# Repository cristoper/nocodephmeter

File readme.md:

This is a pH meter with temperature compensation and digital readout (but no microcontroller) created as part of [Hackaday's 2023 Op-Amp Challenge](https://hackaday.io/contest/190312-op-amp-challenge). It is still under active development. For more information see it's project page:

https://hackaday.io/project/191424-no-code-ph-meter

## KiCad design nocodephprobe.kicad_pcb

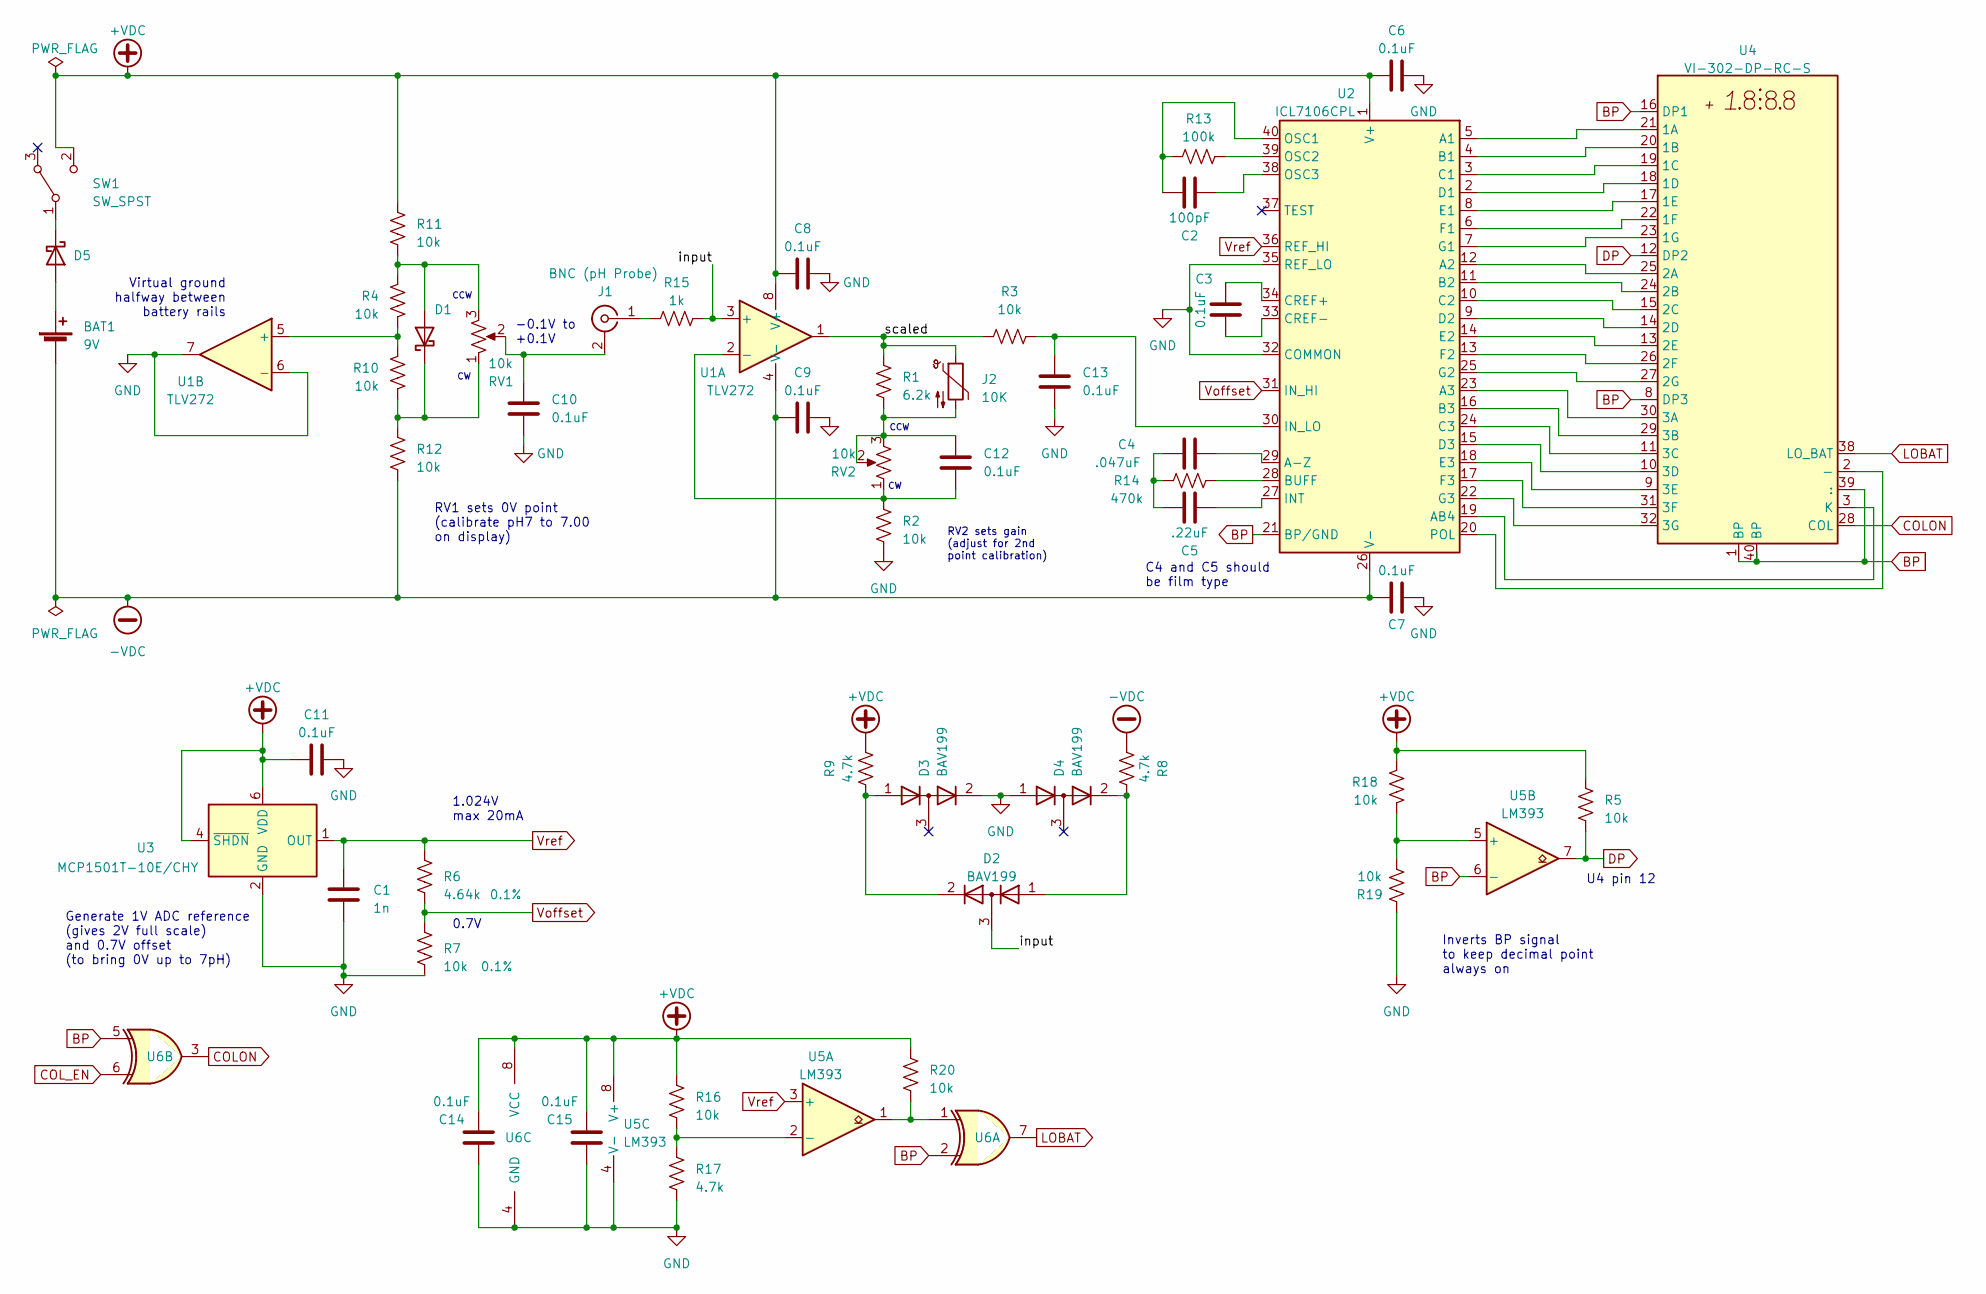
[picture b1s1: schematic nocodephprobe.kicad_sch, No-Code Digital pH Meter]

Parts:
BAT1: 9V; JST_XH_B2B-XH-A_1x02_P2.50mm_Vertical
C1: 1n; C_0805_2012Metric_Pad1.18x1.45mm_HandSolder
C2: 100pF; C_0805_2012Metric_Pad1.18x1.45mm_HandSolder
C3, C6, C7, C8, C9, C10, C11, C12, C13, C14, C15: 0.1uF; C_0805_2012Metric_Pad1.18x1.45mm_HandSolder
C4: .047uF; C_0805_2012Metric_Pad1.18x1.45mm_HandSolder
C5: .22uF; C_Rect_L18.0mm_W6.0mm_P15.00mm_FKS3_FKP3
D1, D5: BAT54-Q; TSOT-23_HandSoldering
D2, D3, D4: BAV199; SOT-23
J1: BNC (pH Probe); BNC_Amphenol_031-6575_Horizontal; digikey 2057-RF1-01K-D-00-50-BK-HDW-ND
J2: 10K; KYCON_STX-3120-3B
R1: 6.2k; R_0805_2012Metric_Pad1.20x1.40mm_HandSolder
R2, R3, R4, R5, R10, R11, R12, R16, R18, R19, R20: 10k; R_0805_2012Metric_Pad1.20x1.40mm_HandSolder
R6: 4.64k; R_0805_2012Metric_Pad1.20x1.40mm_HandSolder; Tolerance 0.1%
R7: 10k; R_0805_2012Metric_Pad1.20x1.40mm_HandSolder; Tolerance 0.1%
R8, R9, R17: 4.7k; R_0805_2012Metric_Pad1.20x1.40mm_HandSolder
R13: 100k; R_0805_2012Metric_Pad1.20x1.40mm_HandSolder
R14: 470k; R_0805_2012Metric_Pad1.20x1.40mm_HandSolder
R15: 1k; R_0805_2012Metric_Pad1.20x1.40mm_HandSolder
RV1, RV2: 10k; JST_XH_B3B-XH-A_1x03_P2.50mm_Vertical
SW1: SW_SPST; JST_XH_B2B-XH-A_1x02_P2.50mm_Vertical
U1: TLV272; SOIC-8_3.9x4.9mm_P1.27mm
U2: ICL7106CPL; DIP-40_W15.24mm
U3: MCP1501T-10E/CHY; SOT-23-6
U4: VI-302-DP-RC-S; DE113-XX-XX
U5: LM393; TSSOP-8_4.4x3mm_P0.65mm
U6: 74HC2G86; TSSOP-8_3x3mm_P0.65mm

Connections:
+VDC: C6.1, C8.1, C11.1, C14.1, C15.1, R5.2, R9.1, R11.2, R16.2, R18.1, R20.2, SW1.2 (C), U1.8 (V+), U2.1 (V+), U3.4 (~SHDN), U3.6 (VDD), U5.8 (V+), U6.8 (VCC)
-VDC: BAT1.2 (-), C7.1, C9.1, R8.2, R12.1, U1.4 (V-), U2.26 (V-)
/input: D2.3 (common), R15.1, U1.3 (+)
/scaled: J2.1, R1.2, R3.1, U1.1
BP: U2.21 (BP/GND), U4.1 (BP), U4.8 (DP3), U4.16 (DP1), U4.39 (:), U4.40 (BP), U5.6 (-), U6.2, U6.5
COLON: U4.28 (COL), U6.3
COL_EN: U6.6
DP: R5.1, U4.12 (DP2), U5.7
GND: C1.2, C6.2, C7.2, C8.2, C9.2, C10.1, C11.2, C13.1, C14.2, C15.2, D3.2 (K), D4.1 (A), R2.1, R7.1, R17.1, R19.2, U1.6 (-), U1.7, U2.32 (COMMON), U2.35 (REF_LO), U3.2 (GND), U3.3 (GND), U3.5 (GND), U5.4 (V-), U6.4 (GND)
LOBAT: U4.38 (LO_BAT), U6.7
unnamed: BAT1.1 (+), D5.1 (A)
unnamed: C4.2, C5.2, R14.2
unnamed: C12.2, J2.5, R1.1, RV2.2, RV2.3
unnamed: D1.1 (A), R4.2, R11.1, RV1.3
unnamed: D1.3 (K), R10.1, R12.2, RV1.1
unnamed: D2.1 (A), D4.2 (K), R8.1
unnamed: D2.2 (K), D3.1 (A), R9.2
unnamed: D5.3 (K), SW1.1 (B)
unnamed: C10.2, J1.2 (Ext), RV1.2
unnamed: J1.1 (In), R15.2
unnamed: R20.1, U5.1, U6.1
unnamed: C12.1, R2.2, RV2.1, U1.2 (-)
unnamed: R4.1, R10.2, U1.5 (+)
unnamed: U2.5 (A1), U4.21 (1A)
unnamed: U2.12 (A2), U4.25 (2A)
unnamed: U2.23 (A3), U4.30 (3A)
unnamed: C4.1, U2.29 (A-Z)
unnamed: U2.19 (AB4), U4.3 (K)
unnamed: U2.4 (B1), U4.20 (1B)
unnamed: U2.11 (B2), U4.24 (2B)
unnamed: U2.16 (B3), U4.29 (3B)
unnamed: R14.1, U2.28 (BUFF)
unnamed: U2.3 (C1), U4.19 (1C)
unnamed: U2.10 (C2), U4.15 (2C)
unnamed: U2.24 (C3), U4.11 (3C)
unnamed: C3.1, U2.34 (CREF+)
unnamed: C3.2, U2.33 (CREF-)
unnamed: U2.2 (D1), U4.18 (1D)
unnamed: U2.9 (D2), U4.14 (2D)
unnamed: U2.15 (D3), U4.10 (3D)
unnamed: U2.8 (E1), U4.17 (1E)
unnamed: U2.14 (E2), U4.13 (2E)
unnamed: U2.18 (E3), U4.9 (3E)
unnamed: U2.6 (F1), U4.22 (1F)
unnamed: U2.13 (F2), U4.26 (2F)
unnamed: U2.17 (F3), U4.31 (3F)
unnamed: U2.7 (G1), U4.23 (1G)
unnamed: U2.25 (G2), U4.27 (2G)
unnamed: U2.22 (G3), U4.32 (3G)
unnamed: C5.1, U2.27 (INT)
unnamed: C13.2, R3.2, U2.30 (IN_LO)
unnamed: C2.2, R13.1, U2.40 (OSC1)
unnamed: R13.2, U2.39 (OSC2)
unnamed: C2.1, U2.38 (OSC3)
unnamed: U2.20 (POL), U4.2 (-)
unnamed: R16.1, R17.2, U5.2 (-)
unnamed: R18.2, R19.1, U5.5 (+)
Voffset: R6.1, R7.2, U2.31 (IN_HI)
Vref: C1.1, R6.2, U2.36 (REF_HI), U3.1 (OUT), U5.3 (+)

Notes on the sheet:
U4 pin 12
C4 and C5 should be film type
1.024V max 20mA
RV2 sets gain (adjust for 2nd point calibration)
Virtual ground halfway between battery rails
RV1 sets 0V point (calibrate pH7 to 7.00 on display)
Generate 1V ADC reference (gives 2V full scale) and 0.7V offset (to bring 0V up to 7pH)
-0.1V to +0.1V
0.7V
CCW
Inverts BP signal to keep decimal point always on

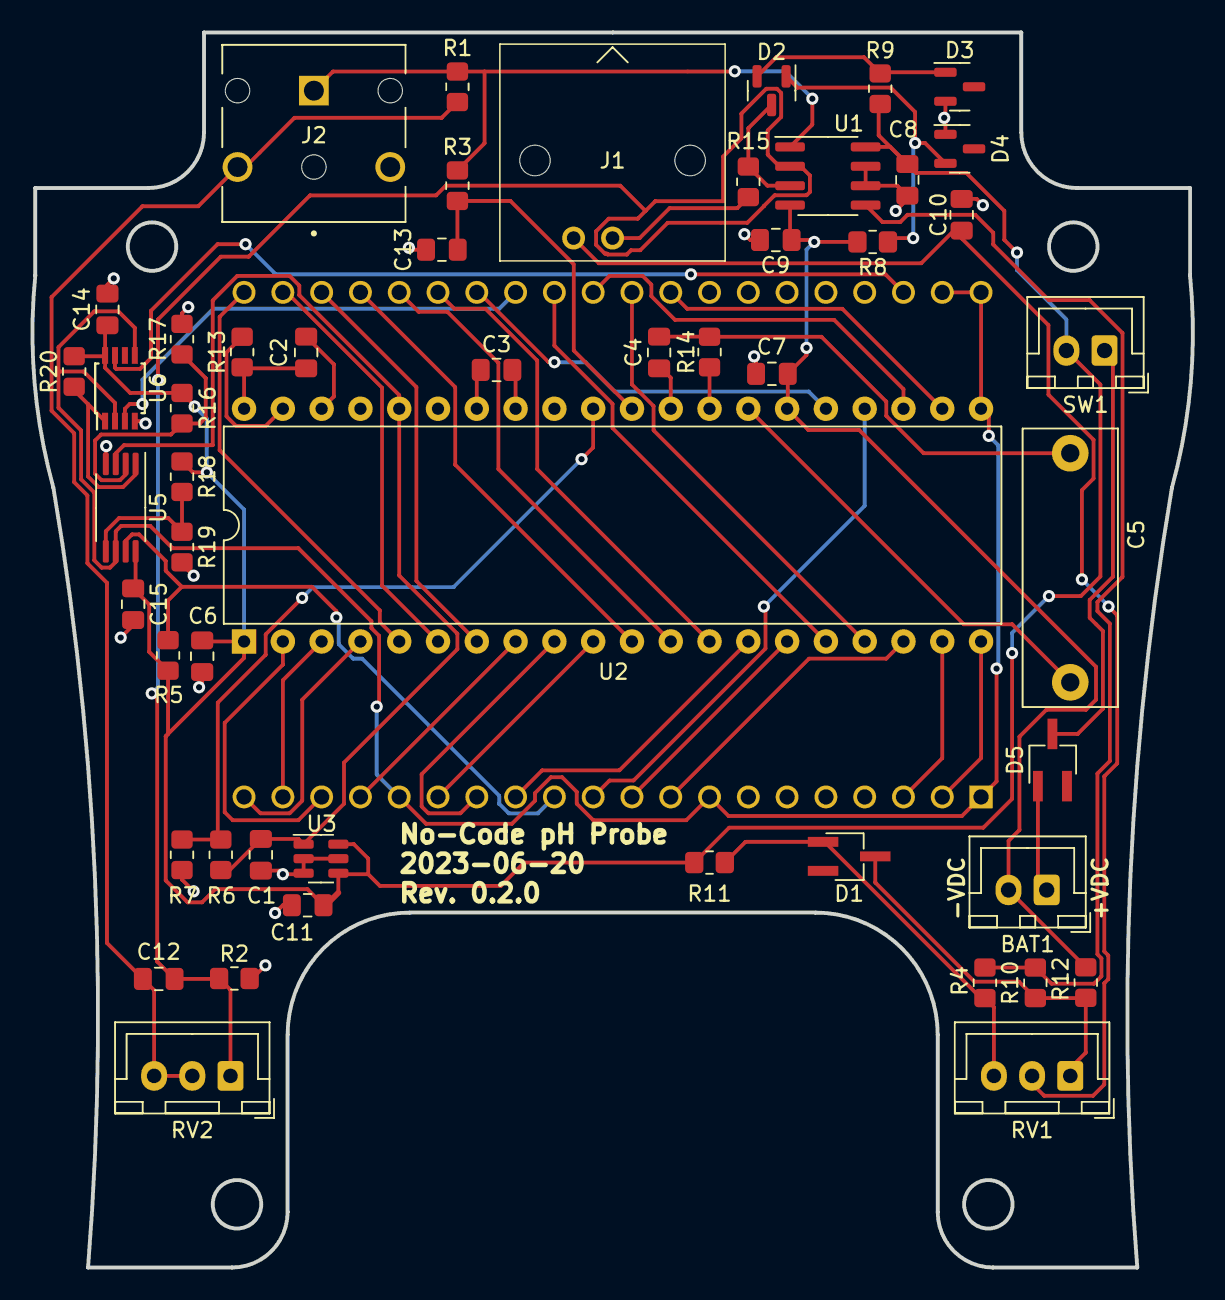
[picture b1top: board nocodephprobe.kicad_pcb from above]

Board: 2 copper layers, 76.0 x 80.9 mm, 52 parts (1 on the bottom side), 58 nets.

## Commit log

2023-05-20 Initial commit: finished basic schematic capture
    Now to choose enclosure and lay out PCB.
2023-05-23 Use 10k pots instead of 100k
2023-05-23 Track board edge drawings
2023-05-23 Use only 1 diode in offset circuit
2023-05-24 Add header footprints to bat and pots
2023-05-24 Add some 3d models
    Including a model for the bnc connector drawn in FreeCAD.
2023-05-24 Fix PCB bosses on board outline!
2023-05-24 Track bnc model
2023-05-25 Add cutout for pots to pcb outline
2023-05-25 track c5 3d model
2023-05-25 Initial routing of nets
    No DRC errors, but some mess vias and traces.
2023-05-26 Remove redundant voltage divider
    This removes two resistors.
2023-05-26 Add revision and github text to silkscreen
2023-05-26 Rework a few traces
2023-05-26 Add guard ring around probe input
2023-05-26 Correct Cref (C3 value)
2023-05-27 Update some gerber settings for jlcpcb
2023-05-27 Add silkscreen labels to power nets
2023-05-28 pcb: move trace away from edge
2023-05-28 pcb: make d1 and r12 more compact
2023-05-28 pcb: move components away from edge and eliminate 2 vias
2023-05-28 pcb: eliminate 2 vias
2023-05-30 schematic: add decoupling caps to op-amp
2023-05-30 Fix op-amp power supply
    Add an 7805 linear regulator to keep voltage within max supply, and add
    decoupling caps.
2023-06-02 Remove fmask all the way around guard trace
    Based on prototype pcbs from jlcpcb, I don't think solder bridges will
    be an issue.
2023-06-03 pcb: fix lcd footprint
    The pins are actually 1.27mm offset (so a 2.54mm wider footprint):
    https://media.digikey.com/pdf/Data%20Sheets/Varitronix%20PDFs/Displays.pdf
2023-06-04 Transpose R6 and R7
    In the prototype the voffset was 0.3V instead of 0.7V!
2023-06-04 pcb: fix LCD pinout!
    Plus it was much easier to route with the correct pin numbering (many
    fewer vias)
2023-06-05 schematic: add pn and datasheet to ntc
2023-06-05 Add decoupling caps to potentiometers
    This also changes the 7805 to a smaller footprint
2023-06-05 Change D1 to a Schottky diode
    This will reduce the range of the zero calibration from +/- 0.3V to +/-
    0.15V and make the setting less finicky.
2023-06-05 Flip pots so that CW increases pH during calibration
2023-06-05 Track label template
2023-06-05 pcb: update silkscreen for new github url
2023-06-05 Add MIT license.txt
2023-06-06 Add header for power switch
2023-06-06 Add basic readme
2023-06-06 Regulate entire circuit to 5V
    Though in the future I'd like to run the 7106 directly from the battery,
    that requires centering the 7805 and lmv358a at the virtual ground.
2023-06-06 Ignore hackaday/ dir
2023-06-06 pcb: update PCB to reflect schematic (power 7106 from 5V)
    I am really unhappy with the power routing and need to rework the whole
    power system so the 7106 can be powered directly from the battery
    anyway.
2023-06-06 schematic: tidy power switch
2023-06-09 schematic: simplify power and decoupling
    The big change is switch from the lmv358a to the tlv272:
    - TLV272 can operate from up to 16.5V supply, which means we can run it
    directly from the 9V battery (no 7805 or zeners required)
    - It has better typical Vos (500uV), Input Offset Current (1pA), and
    Input Bias Current (1PA)
    - It has worse max offset specs (Vos=5mV, Iio/Iib = 60pA), but they
2023-06-09 pcb: make cutouts for pots larger
    This makes it less critical to drill holes in panel at exact location
2023-06-11 pcb: route improved power and headers
2023-06-11 pcb: move switch header to above C5
2023-06-11 pcb: use 2-pin header for RV2
2023-06-14 Implement [optional] input protection
    D2 will clamp the input to 3 diode drops from either rail (~1.8V). This
    keeps the input within the safe range for the TLV272. R15 limits the
    current in case of overvoltage. The diodes in D3 and D4 set a bias point
    two diode drops below the positive rail and above the negative rail to
    minimize the reverse voltage (and therefore leakage current) across the
    D2 diodes.
2023-06-14 Specify cheaper Schottky diodes
    Also add one as reverse-voltage protection to protect op-amp input (D5)
2023-06-14 Use SPDT for power switch
    I decided on these MTS-103 mini toggle switches, to be mounted next to BNC
    (and connected with wires to JST XH connector):
    https://www.amazon.com/dp/B07CJFVZ7M
2023-06-15 Revert to using 3-pin connector for RV2
    I think it is more flexible. Can always use a 3-pin plug with only 2
    wires populated.
2023-06-20 Low battery indicator
    This change adds a comparator and xor gate to implement a low-battery
    indicator. When the positive rail goes below about 3V, then the output
    of U5A goes high. The output of U5A is XOR'd with the backplane which
    inverts the backplane when it is high, turning on the LOBAT LCD
    indicator.
    I'm using the spare coparator to replace the 2n7002 to keep the decimal
2023-06-20 cheaper, smaller film caps
    After reading this app note (The Integrating A/D Converter (ICL7135))
    I'm convinced a big poolypropylene capacitor is not necessary. But I do
    think using a film type for the autozero is a good idea.
    "is of no consequence in this circuit. The dielectric absorption of
    the reference and auto-zero capacitors are only important at
    power-on or when the circuit is recovering from an overload.
2023-06-20 pcb: new 3D model for smaller caps
2023-06-21 Use larger, film cap for Cref
2023-06-21 Reduce decoupling to gnd
    This is an attempt to reduce the capacitive load on the output of U1B
    (the virtual gnd) to keep it more stable. The isolation resistor R21
    should also help even if it introduces low-frequency gnd errors.
